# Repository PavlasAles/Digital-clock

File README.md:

# Digital-clock
Digital clock with RTC modul and with Arduino. Digitální hodiny s použitím RTC modulu a Arduina.

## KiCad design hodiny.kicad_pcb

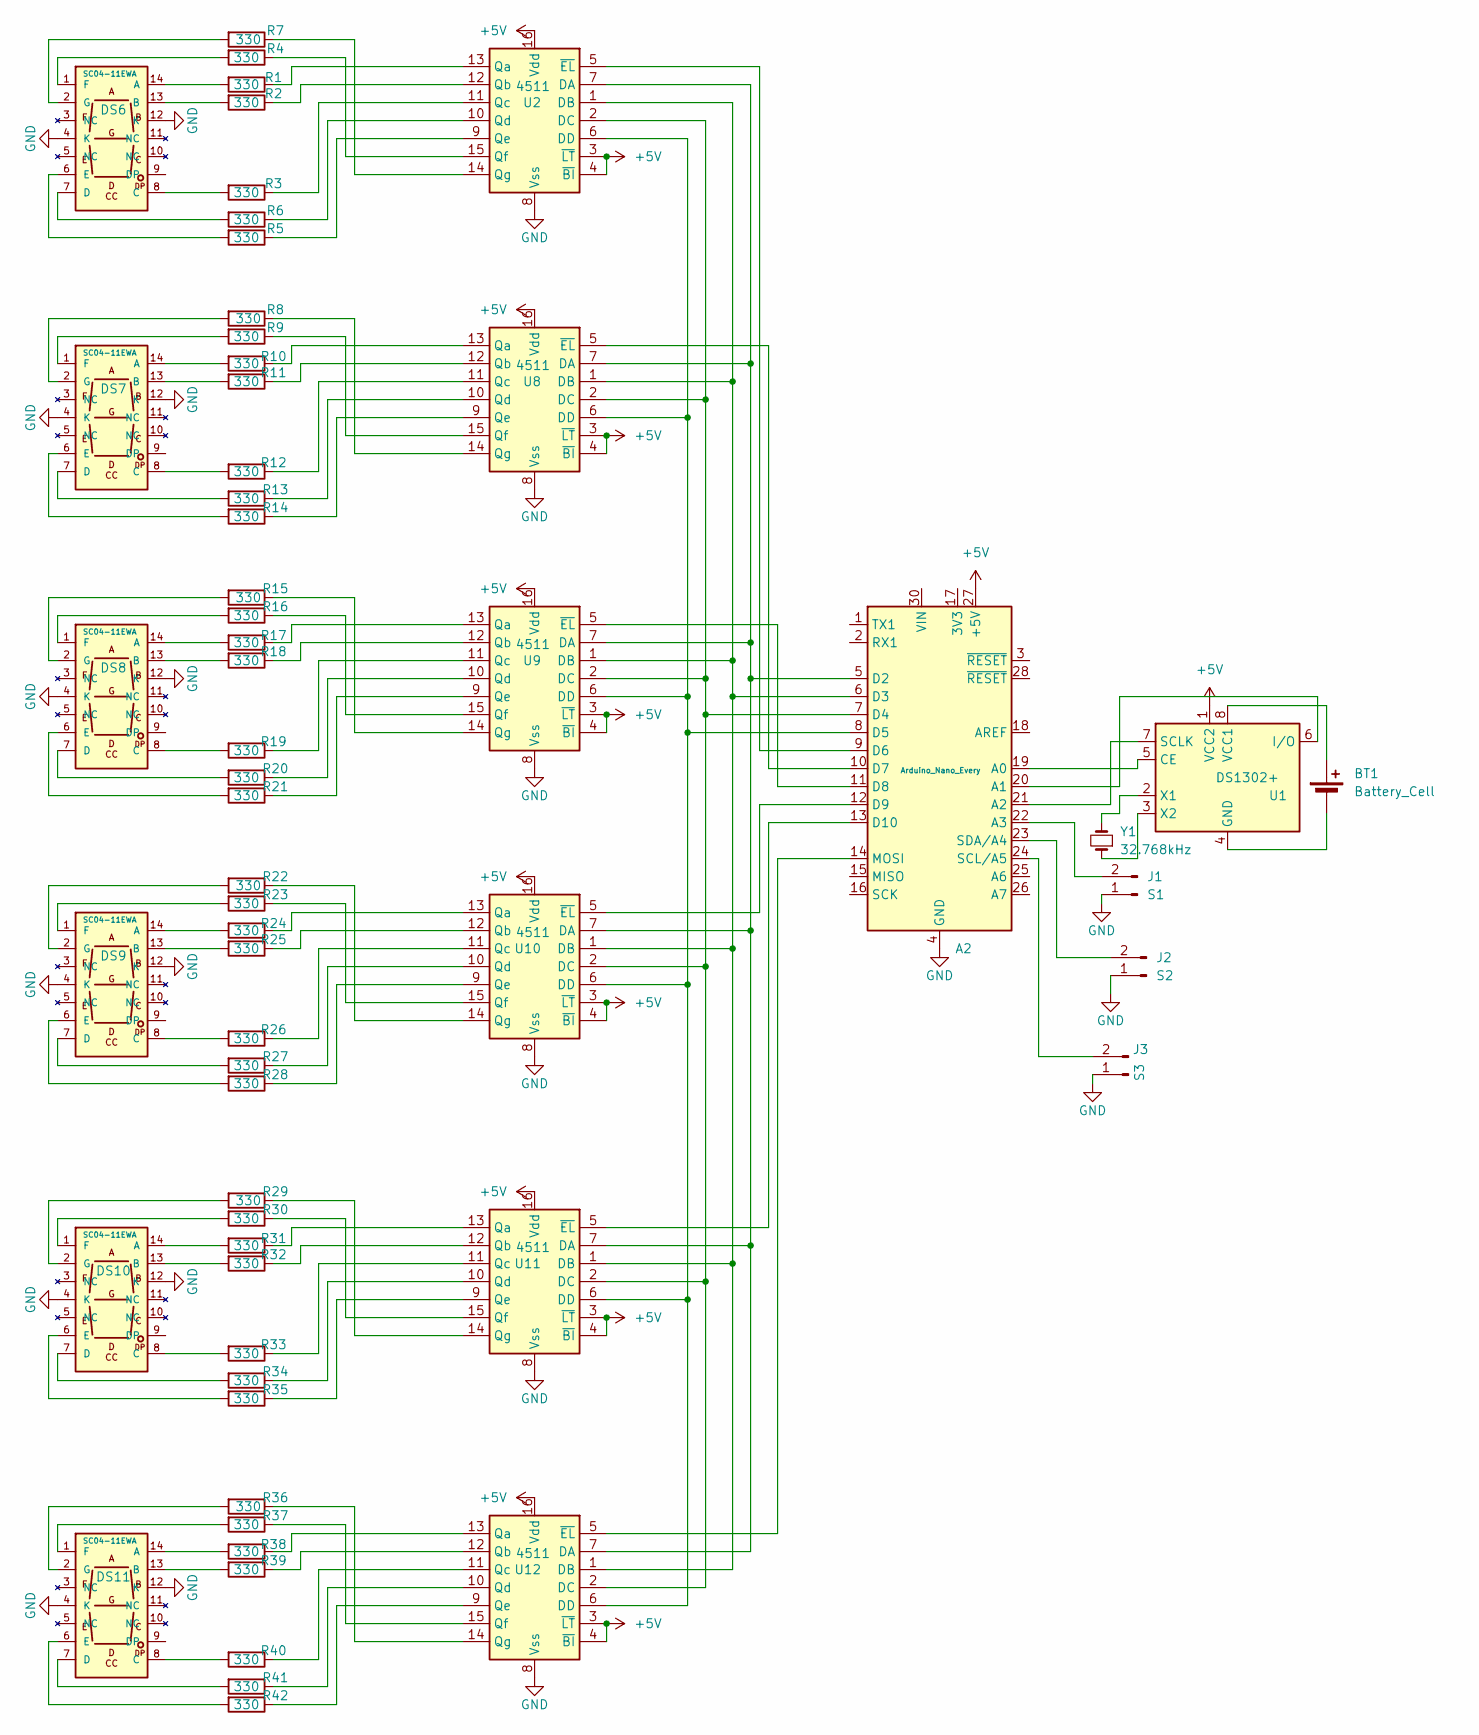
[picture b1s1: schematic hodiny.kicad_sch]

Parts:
A2: Arduino_Nano_Every; Arduino_Nano
BT1: Battery_Cell; BatteryHolder_ComfortableElectronic_CH273-2450_1x2450
DS6, DS7, DS8, DS9, DS10, DS11: SC04-11EWA; SC04-11EWA_THT
J1: S1; PinHeader_1x02_P2.54mm_Horizontal
J2: S2; PinHeader_1x02_P2.54mm_Horizontal
J3: S3; PinHeader_1x02_P2.54mm_Horizontal
R1, R2, R3, R4, R5, R6, R7, R8, R9, R10, R11, R12, R13, R14, R15, R16, R17, R18, R19, R20, R21, R22, R23, R24, R25, R26, R27, R28, R29, R30, R31, R32, R33, R34, R35, R36, R37, R38, R39, R40, R41, R42: 330; R_Axial_DIN0411_L9.9mm_D3.6mm_P15.24mm_Horizontal
U1: DS1302+; DIP-8_W7.62mm_Socket_LongPads
U2, U8, U9, U10, U11, U12: 4511; DIP-16_W7.62mm_Socket_LongPads
Y1: 32.768kHz; Crystal_C26-LF_D2.1mm_L6.5mm_Horizontal

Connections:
+5V: A2.27 (+5V), U1.1 (VCC2), U2.3 (~LT), U2.4 (~BI), U2.16 (Vdd), U8.3 (~LT), U8.4 (~BI), U8.16 (Vdd), U9.3 (~LT), U9.4 (~BI), U9.16 (Vdd), U10.3 (~LT), U10.4 (~BI), U10.16 (Vdd), U11.3 (~LT), U11.4 (~BI), U11.16 (Vdd), U12.3 (~LT), U12.4 (~BI), U12.16 (Vdd)
GND: A2.4 (GND), A2.29 (GND), DS6.4 (K), DS6.12 (K), DS7.4 (K), DS7.12 (K), DS8.4 (K), DS8.12 (K), DS9.4 (K), DS9.12 (K), DS10.4 (K), DS10.12 (K), DS11.4 (K), DS11.12 (K), J1.1, J2.1, J3.1, U2.8 (Vss), U8.8 (Vss), U9.8 (Vss), U10.8 (Vss), U11.8 (Vss), U12.8 (Vss)
unnamed: A2.19 (A0), U1.5 (CE)
unnamed: A2.20 (A1), U1.6 (I/O)
unnamed: A2.21 (A2), U1.7 (SCLK)
unnamed: A2.22 (A3), J1.2
unnamed: A2.5 (D2), U2.7 (DA), U8.7 (DA), U9.7 (DA), U10.7 (DA), U11.7 (DA), U12.7 (DA)
unnamed: A2.6 (D3), U2.1 (DB), U8.1 (DB), U9.1 (DB), U10.1 (DB), U11.1 (DB), U12.1 (DB)
unnamed: A2.7 (D4), U2.2 (DC), U8.2 (DC), U9.2 (DC), U10.2 (DC), U11.2 (DC), U12.2 (DC)
unnamed: A2.8 (D5), U2.6 (DD), U8.6 (DD), U9.6 (DD), U10.6 (DD), U11.6 (DD), U12.6 (DD)
unnamed 10: A2.9 (D6), U2.5 (~EL); also elsewhere on the board
unnamed 11: A2.10 (D7), U8.5 (~EL); also elsewhere on the board
unnamed: A2.11 (D8), U9.5 (~EL)
unnamed: A2.12 (D9), U10.5 (~EL)
unnamed: A2.13 (D10), U11.5 (~EL)
unnamed: A2.14 (MOSI), U12.5 (~EL)
unnamed: A2.24 (SCL/A5), J3.2
unnamed: A2.23 (SDA/A4), J2.2
unnamed: BT1.1 (+), U1.8 (VCC1)
unnamed: BT1.2 (-), U1.4 (GND)
unnamed: DS6.14 (A), R1.2
unnamed: DS6.13 (B), R2.2
unnamed: DS6.8 (C), R3.2
unnamed: DS6.7 (D), R6.2
unnamed: DS6.6 (E), R5.2
unnamed: DS6.1 (F), R4.2
unnamed: DS6.2 (G), R7.2
unnamed: DS7.14 (A), R10.2
unnamed: DS7.13 (B), R11.2
unnamed: DS7.8 (C), R12.2
unnamed: DS7.7 (D), R13.2
unnamed: DS7.6 (E), R14.2
unnamed: DS7.1 (F), R9.2
unnamed: DS7.2 (G), R8.2
unnamed: DS8.14 (A), R17.2
unnamed: DS8.13 (B), R18.2
unnamed: DS8.8 (C), R19.2
unnamed: DS8.7 (D), R20.2
unnamed: DS8.6 (E), R21.2
unnamed: DS8.1 (F), R16.2
unnamed: DS8.2 (G), R15.2
unnamed: DS9.14 (A), R24.2
unnamed: DS9.13 (B), R25.2
unnamed: DS9.8 (C), R26.2
unnamed: DS9.7 (D), R27.2
unnamed: DS9.6 (E), R28.2
unnamed: DS9.1 (F), R23.2
unnamed: DS9.2 (G), R22.2
unnamed: DS10.14 (A), R31.2
unnamed: DS10.13 (B), R32.2
unnamed: DS10.8 (C), R33.2
unnamed: DS10.7 (D), R34.2
unnamed: DS10.6 (E), R35.2
unnamed: DS10.1 (F), R30.2
unnamed: DS10.2 (G), R29.2
unnamed: DS11.14 (A), R38.2
unnamed: DS11.13 (B), R39.2
unnamed: DS11.8 (C), R40.2
unnamed: DS11.7 (D), R41.2
unnamed: DS11.6 (E), R42.2
unnamed: DS11.1 (F), R37.2
unnamed: DS11.2 (G), R36.2
unnamed: U1.2 (X1), Y1.2
unnamed: U1.3 (X2), Y1.1
unnamed: R1.1, U2.13 (Qa)
unnamed: R2.1, U2.12 (Qb)
unnamed: R3.1, U2.11 (Qc)
unnamed: R6.1, U2.10 (Qd)
unnamed: R5.1, U2.9 (Qe)
unnamed: R4.1, U2.15 (Qf)
unnamed: R7.1, U2.14 (Qg)
unnamed: R10.1, U8.13 (Qa)
unnamed: R11.1, U8.12 (Qb)
unnamed: R12.1, U8.11 (Qc)
unnamed: R13.1, U8.10 (Qd)
unnamed: R14.1, U8.9 (Qe)
unnamed: R9.1, U8.15 (Qf)
unnamed: R8.1, U8.14 (Qg)
unnamed: R17.1, U9.13 (Qa)
unnamed: R18.1, U9.12 (Qb)
unnamed: R19.1, U9.11 (Qc)
unnamed: R20.1, U9.10 (Qd)
unnamed: R21.1, U9.9 (Qe)
unnamed: R16.1, U9.15 (Qf)
unnamed: R15.1, U9.14 (Qg)
unnamed: R24.1, U10.13 (Qa)
unnamed: R25.1, U10.12 (Qb)
unnamed: R26.1, U10.11 (Qc)
unnamed: R27.1, U10.10 (Qd)
unnamed: R28.1, U10.9 (Qe)
unnamed: R23.1, U10.15 (Qf)
unnamed: R22.1, U10.14 (Qg)
unnamed: R31.1, U11.13 (Qa)
unnamed: R32.1, U11.12 (Qb)
unnamed: R33.1, U11.11 (Qc)
unnamed: R34.1, U11.10 (Qd)
unnamed: R35.1, U11.9 (Qe)
unnamed: R30.1, U11.15 (Qf)
unnamed: R29.1, U11.14 (Qg)
unnamed: R38.1, U12.13 (Qa)
unnamed: R39.1, U12.12 (Qb)
unnamed: R40.1, U12.11 (Qc)
unnamed: R41.1, U12.10 (Qd)
unnamed: R42.1, U12.9 (Qe)
unnamed: R37.1, U12.15 (Qf)
unnamed: R36.1, U12.14 (Qg)

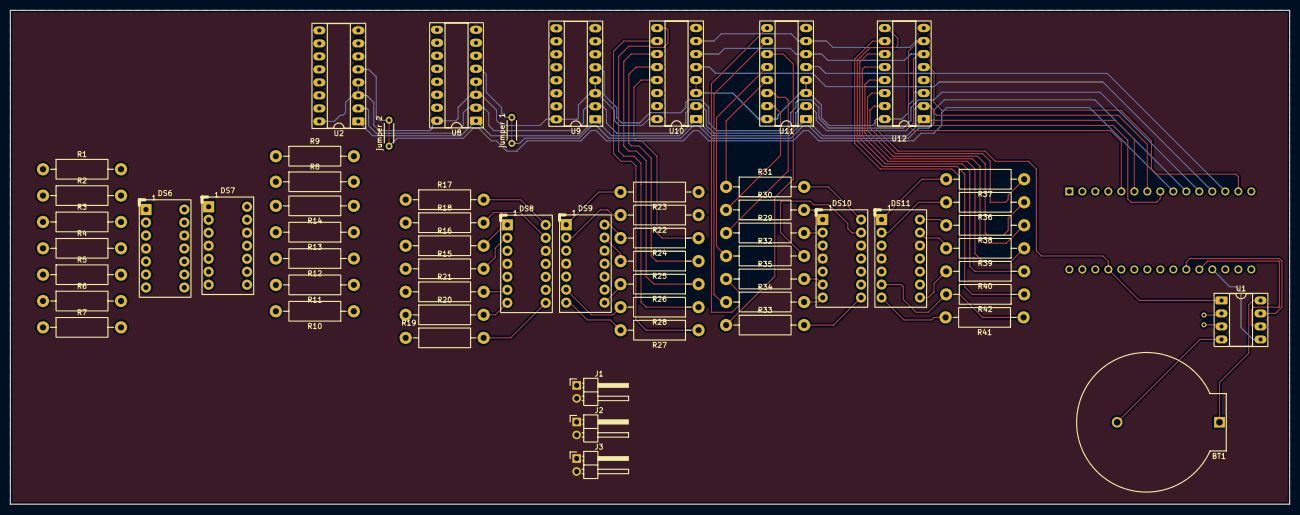
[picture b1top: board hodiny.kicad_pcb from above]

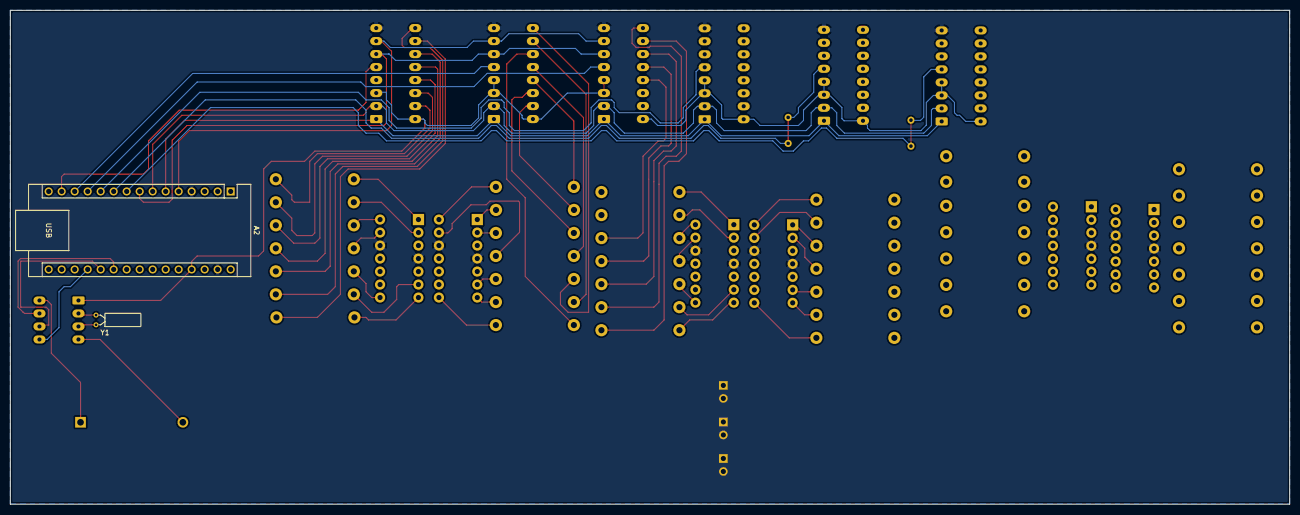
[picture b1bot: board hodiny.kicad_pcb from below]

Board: 2 copper layers, 250.0 x 96.5 mm, 63 parts (2 on the bottom side), 106 nets.

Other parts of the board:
jumper 1, jumper 2: 0R; R_Axial_DIN0204_L3.6mm_D1.6mm_P5.08mm_Horizontal

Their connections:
unnamed 10: jumper 2.1, jumper 2.2; also elsewhere on the board
unnamed 11: jumper 1.1, jumper 1.2; also elsewhere on the board

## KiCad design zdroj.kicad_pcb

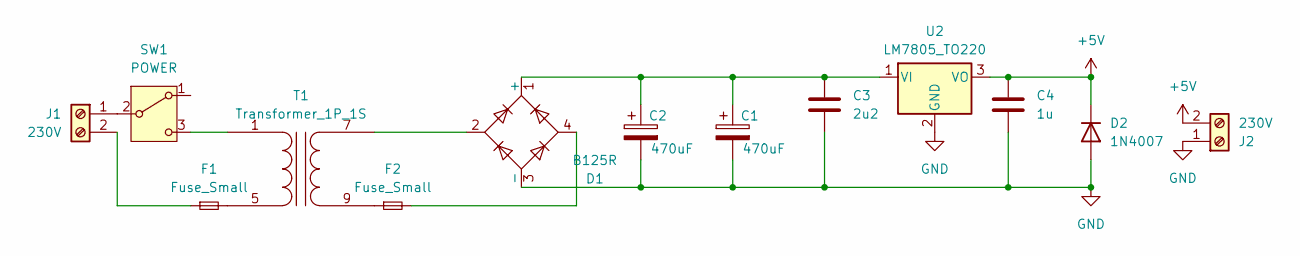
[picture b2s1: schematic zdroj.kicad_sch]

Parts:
C1, C2: 470uF; CP_Radial_D8.0mm_P3.50mm
C3: 2u2; C_Rect_L9.0mm_W4.0mm_P7.50mm_MKT
C4: 1u; C_Rect_L9.0mm_W4.0mm_P7.50mm_MKT
D1: B125R; Diode_Bridge_Round_D9.0mm
D2: 1N4007; D_DO-41_SOD81_P12.70mm_Horizontal
F1, F2: Fuse_Small; Fuseholder_Clip-5x20mm_Eaton_1A5601-01_Inline_P20.80x6.76mm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
J1, J2: 230V; TerminalBlock_Phoenix_MKDS-1,5-2_1x02_P5.00mm_Horizontal
SW1: POWER; SW_NKK_GW12LJP
T1: Transformer_1P_1S; Transformer_Breve_TEZ-28x33
U2: LM7805_TO220; TO-220-3_Vertical

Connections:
+5V: C4.1, D2.1 (K), J2.2, U2.3 (VO)
GND: C1.2, C2.2, C3.2, C4.2, D1.3 (-), D2.2 (A), J2.1, U2.2 (GND)
unnamed: C1.1, C2.1, C3.1, D1.1 (+), U2.1 (VI)
unnamed: D1.4, F2.2
unnamed: J1.1, SW1.2 (B)
unnamed: F1.1, J1.2
unnamed: SW1.3 (C), T1.1 (AA)
unnamed: F1.2, T1.5 (AB)
unnamed: F2.1, T1.9 (SA)
unnamed: D1.2, T1.7 (SB)

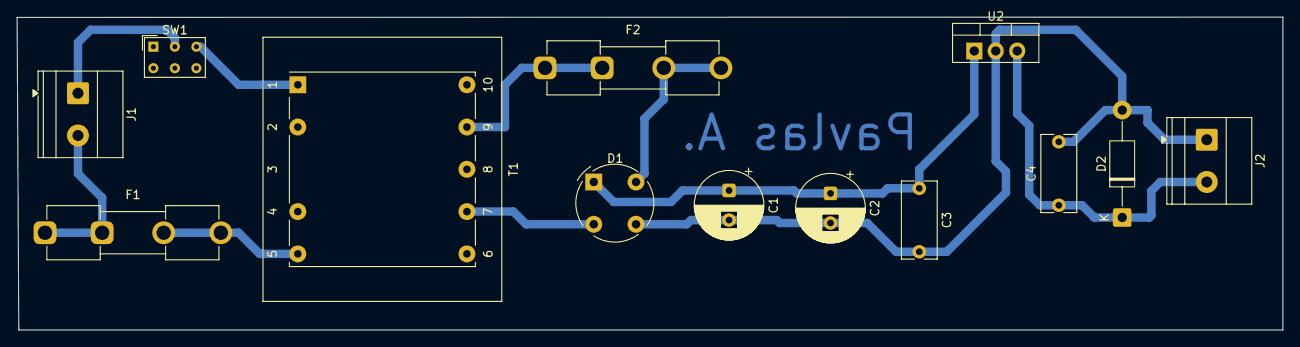
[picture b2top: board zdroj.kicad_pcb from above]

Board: 2 copper layers, 149.7 x 37.0 mm, 13 parts (0 on the bottom side), 10 nets.
